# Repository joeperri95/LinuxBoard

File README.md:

# LinuxBoard

A basic stm32mp151 board to help me get more familiar with
- application processors 
- high speed digital design
- working with BGAs

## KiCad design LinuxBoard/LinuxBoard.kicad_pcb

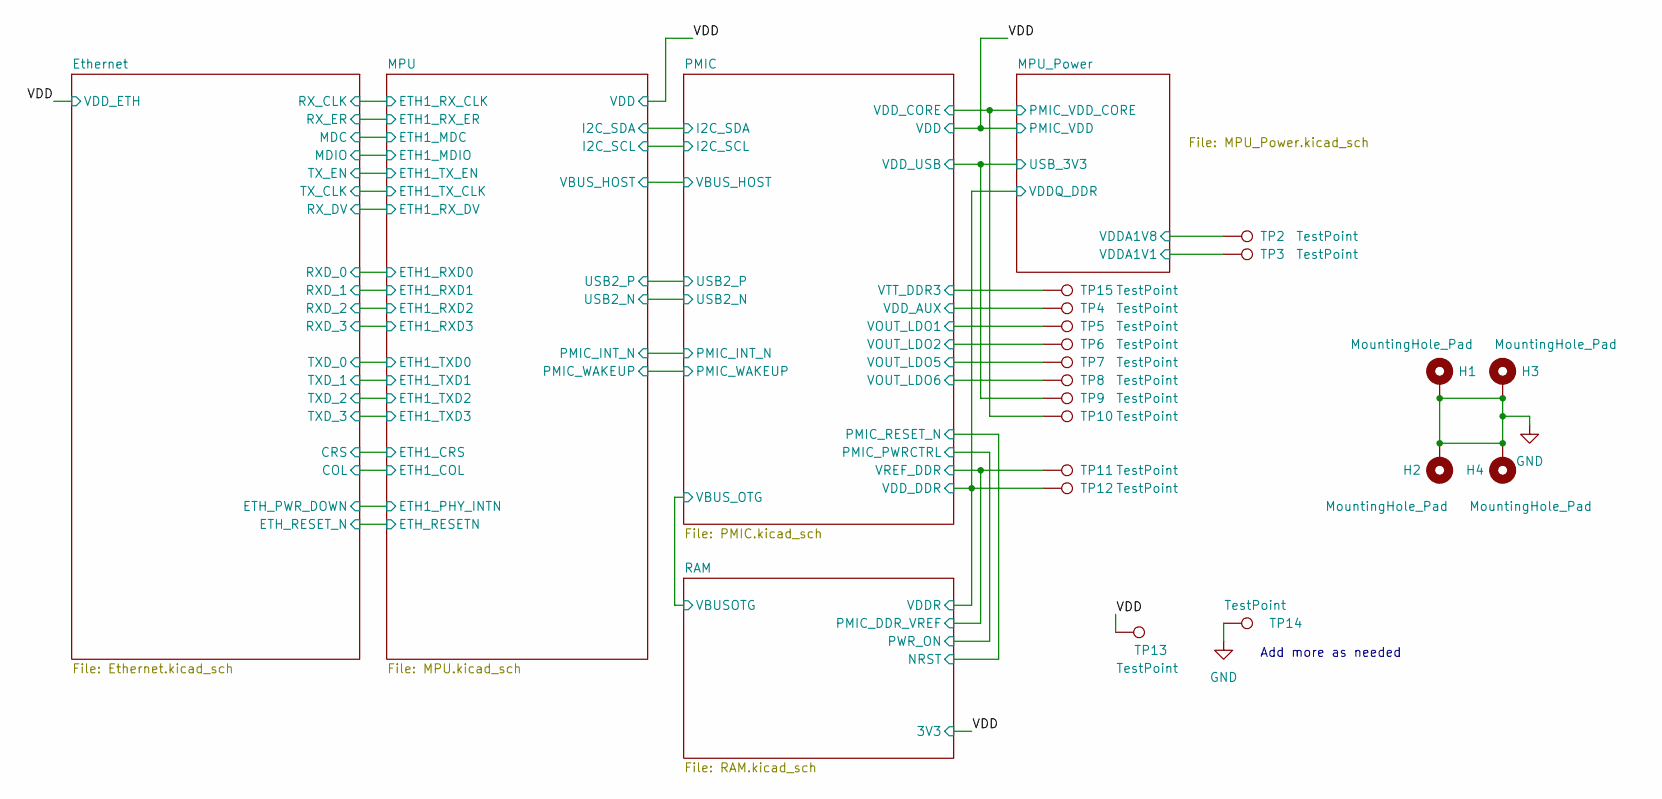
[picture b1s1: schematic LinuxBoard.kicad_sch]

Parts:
H1, H2, H3, H4: MountingHole_Pad; MountingHole_2.5mm_Pad
TP2, TP3, TP4, TP5, TP6, TP7, TP8, TP9, TP10, TP11, TP12, TP13, TP14, TP15: TestPoint; TestPoint_Pad_D2.0mm

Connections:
/MPU_Power/VDDA1V1: TP3.1; also elsewhere on the board
/MPU_Power/VDDA1V8: TP2.1; also elsewhere on the board
/MPU_Power/VDDQ_DDR: TP12.1; also elsewhere on the board
/MPU_Power/VDD_CORE: TP10.1; also elsewhere on the board
/PMIC/LDO1OUT: TP5.1; also elsewhere on the board
/PMIC/LDO2OUT: TP6.1; also elsewhere on the board
/PMIC/LDO3OUT: TP15.1; also elsewhere on the board
/PMIC/LDO4OUT: TP9.1; also elsewhere on the board
/PMIC/LDO5OUT: TP7.1; also elsewhere on the board
/PMIC/LDO6OUT: TP8.1; also elsewhere on the board
/PMIC/VDD_AUX: TP4.1; also elsewhere on the board
/PMIC/VREFDDR: TP11.1; also elsewhere on the board
/VDD: TP13.1; also elsewhere on the board
GND: H1.1, H2.1, H3.1, H4.1, TP14.1; also elsewhere on the board

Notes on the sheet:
Add more as needed

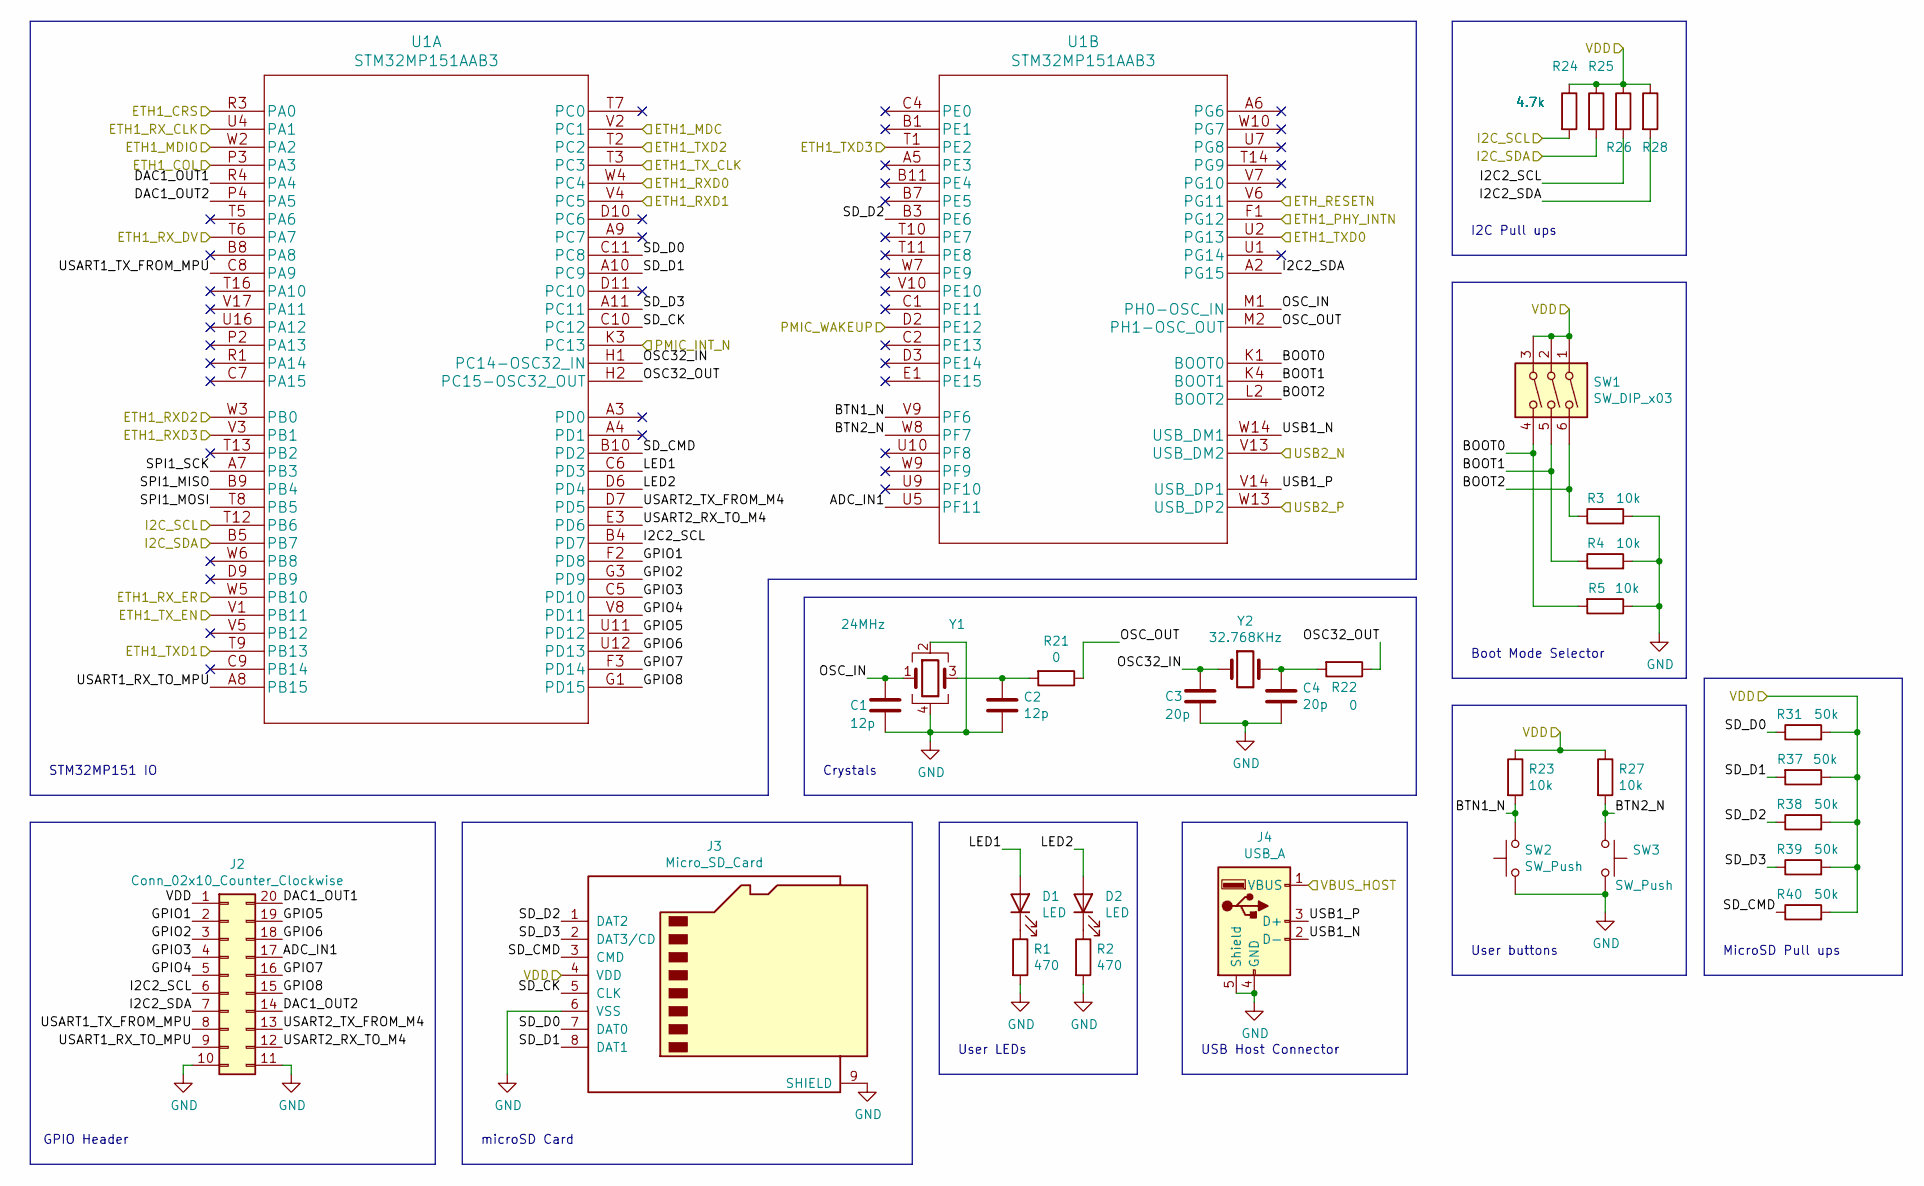
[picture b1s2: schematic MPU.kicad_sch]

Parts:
C1, C2: 12p; C_0603_1608Metric
C3, C4: 20p; C_0603_1608Metric
D1, D2: LED; LED_0603_1608Metric
J2: Conn_02x10_Counter_Clockwise; IDC-Header_2x10_P2.54mm_Vertical
J3: Micro_SD_Card; microSD_HC_Wuerth_693072010801
J4: USB_A; USB_A_Stewart_SS-52100-001_Horizontal
R1, R2: 470; R_0603_1608Metric_Pad0.98x0.95mm_HandSolder
R3, R4, R5, R23, R27: 10k; R_0603_1608Metric_Pad0.98x0.95mm_HandSolder
R21, R22: 0; R_0603_1608Metric_Pad0.98x0.95mm_HandSolder
R24, R25, R26, R28: 4.7k; R_0603_1608Metric_Pad0.98x0.95mm_HandSolder
R31, R37, R38, R39, R40: 50k; R_0603_1608Metric_Pad0.98x0.95mm_HandSolder
SW1: SW_DIP_x03; SW_DIP_SPSTx03_Slide_Omron_A6S-310x_W8.9mm_P2.54mm
SW2, SW3: SW_Push; SW_Push_1P1T_NO_6x6mm_H9.5mm
U1: STM32MP151AAB3
Y1: 24MHz; Crystal_SMD_2016-4Pin_2.0x1.6mm
Y2: 32.768KHz; Crystal_SMD_TXC_9HT11-2Pin_2.0x1.2mm

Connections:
/Ethernet/COL: U1.P3 (PA3); also elsewhere on the board
/Ethernet/CRS: U1.R3 (PA0); also elsewhere on the board
/Ethernet/ETH_PWR_DOWN: U1.F1 (PG12); also elsewhere on the board
/Ethernet/ETH_RESET_N: U1.V6 (PG11); also elsewhere on the board
/Ethernet/MDC: U1.V2 (PC1); also elsewhere on the board
/Ethernet/MDIO: U1.W2 (PA2); also elsewhere on the board
/Ethernet/RXD_0: U1.W4 (PC4); also elsewhere on the board
/Ethernet/RXD_1: U1.V4 (PC5); also elsewhere on the board
/Ethernet/RXD_2: U1.W3 (PB0); also elsewhere on the board
/Ethernet/RXD_3: U1.V3 (PB1); also elsewhere on the board
/Ethernet/RX_CLK: U1.U4 (PA1); also elsewhere on the board
/Ethernet/RX_DV: U1.T6 (PA7); also elsewhere on the board
/Ethernet/RX_ER: U1.W5 (PB10); also elsewhere on the board
/Ethernet/TXD_0: U1.U2 (PG13); also elsewhere on the board
/Ethernet/TXD_1: U1.T9 (PB13); also elsewhere on the board
/Ethernet/TXD_2: U1.T2 (PC2); also elsewhere on the board
/Ethernet/TXD_3: U1.T1 (PE2); also elsewhere on the board
/Ethernet/TX_CLK: U1.T3 (PC3); also elsewhere on the board
/Ethernet/TX_EN: U1.V1 (PB11); also elsewhere on the board
/MPU/ADC_IN1: J2.17, U1.U5 (PF11)
/MPU/BOOT0: R5.2, SW1.4, U1.K1 (BOOT0)
/MPU/BOOT1: R4.1, SW1.5, U1.K4 (BOOT1)
/MPU/BOOT2: R3.1, SW1.6, U1.L2 (BOOT2)
/MPU/BTN1_N: R23.2, SW2.2, U1.V9 (PF6)
/MPU/BTN2_N: R27.2, SW3.1, U1.W8 (PF7)
/MPU/DAC1_OUT1: J2.20, U1.R4 (PA4)
/MPU/DAC1_OUT2: J2.14, U1.P4 (PA5)
/MPU/GPIO1: J2.2, U1.F2 (PD8)
/MPU/GPIO2: J2.3, U1.G3 (PD9)
/MPU/GPIO3: J2.4, U1.C5 (PD10)
/MPU/GPIO4: J2.5, U1.V8 (PD11)
/MPU/GPIO5: J2.19, U1.U11 (PD12)
/MPU/GPIO6: J2.18, U1.U12 (PD13)
/MPU/GPIO7: J2.16, U1.F3 (PD14)
/MPU/GPIO8: J2.15, U1.G1 (PD15)
/MPU/I2C2_SCL: J2.6, R26.2, U1.B4 (PD7)
/MPU/I2C2_SDA: J2.7, R28.2, U1.A2 (PG15)
/MPU/I2C_SCL: R24.2, U1.T12 (PB6); also elsewhere on the board
/MPU/I2C_SDA: R25.2, U1.B5 (PB7); also elsewhere on the board
/MPU/LED1: D1.2 (A), U1.C6 (PD3)
/MPU/LED2: D2.2 (A), U1.D6 (PD4)
/MPU/OSC32_IN: C3.1, U1.H1 (PC14-OSC32_IN), Y2.1
/MPU/OSC32_OUT: R22.1, U1.H2 (PC15-OSC32_OUT)
/MPU/OSC_IN: C1.1, U1.M1 (PH0-OSC_IN), Y1.1
/MPU/OSC_OUT: R21.1, U1.M2 (PH1-OSC_OUT)
/MPU/PMIC_INT_N: U1.K3 (PC13); also elsewhere on the board
/MPU/PMIC_WAKEUP: U1.D2 (PE12); also elsewhere on the board
/MPU/SD_CK: J3.5 (CLK), U1.C10 (PC12)
/MPU/SD_CMD: J3.3 (CMD), R40.1, U1.B10 (PD2)
/MPU/SD_D0: J3.7 (DAT0), R31.1, U1.C11 (PC8)
/MPU/SD_D1: J3.8 (DAT1), R37.2, U1.A10 (PC9)
/MPU/SD_D2: J3.1 (DAT2), R38.1, U1.B3 (PE6)
/MPU/SD_D3: J3.2 (DAT3/CD), R39.1, U1.A11 (PC11)
/MPU/SPI1_MISO: U1.B9 (PB4)
/MPU/SPI1_MOSI: U1.T8 (PB5)
/MPU/SPI1_SCK: U1.A7 (PB3)
/MPU/USART1_RX_TO_MPU: J2.9, U1.A8 (PB15)
/MPU/USART1_TX_FROM_MPU: J2.8, U1.C8 (PA9)
/MPU/USART2_RX_TO_M4: J2.12, U1.E3 (PD6)
/MPU/USART2_TX_FROM_M4: J2.13, U1.D7 (PD5)
/MPU/USB1_N: J4.2 (D-), U1.W14 (USB_DM1)
/MPU/USB1_P: J4.3 (D+), U1.V14 (USB_DP1)
/MPU/USB2_N: U1.V13 (USB_DM2); also elsewhere on the board
/MPU/USB2_P: U1.W13 (USB_DP2); also elsewhere on the board
/MPU/VBUS_HOST: J4.1 (VBUS); also elsewhere on the board
/VDD: J2.1, J3.4 (VDD), R23.1, R24.1, R25.1, R26.1, R27.1, R28.1, R31.2, R37.1, R38.2, R39.2, R40.2, SW1.1, SW1.2, SW1.3; also elsewhere on the board
GND: C1.2, C2.2, C3.2, C4.2, J2.10, J2.11, J3.6 (VSS), J3.9 (SHIELD), J4.4 (GND), J4.5 (Shield), R1.2, R2.2, R3.2, R4.2, R5.1, SW2.1, SW3.2, Y1.2, Y1.4; also elsewhere on the board
unnamed: C2.1, R21.2, Y1.3
unnamed: C4.1, R22.2, Y2.2
unnamed: D1.1 (K), R1.1
unnamed: D2.1 (K), R2.1

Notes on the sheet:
Crystals
MicroSD Pull ups
GPIO Header
User LEDs
STM32MP151 IO
I2C Pull ups
USB Host Connector
Boot Mode Selector
microSD Card
User buttons

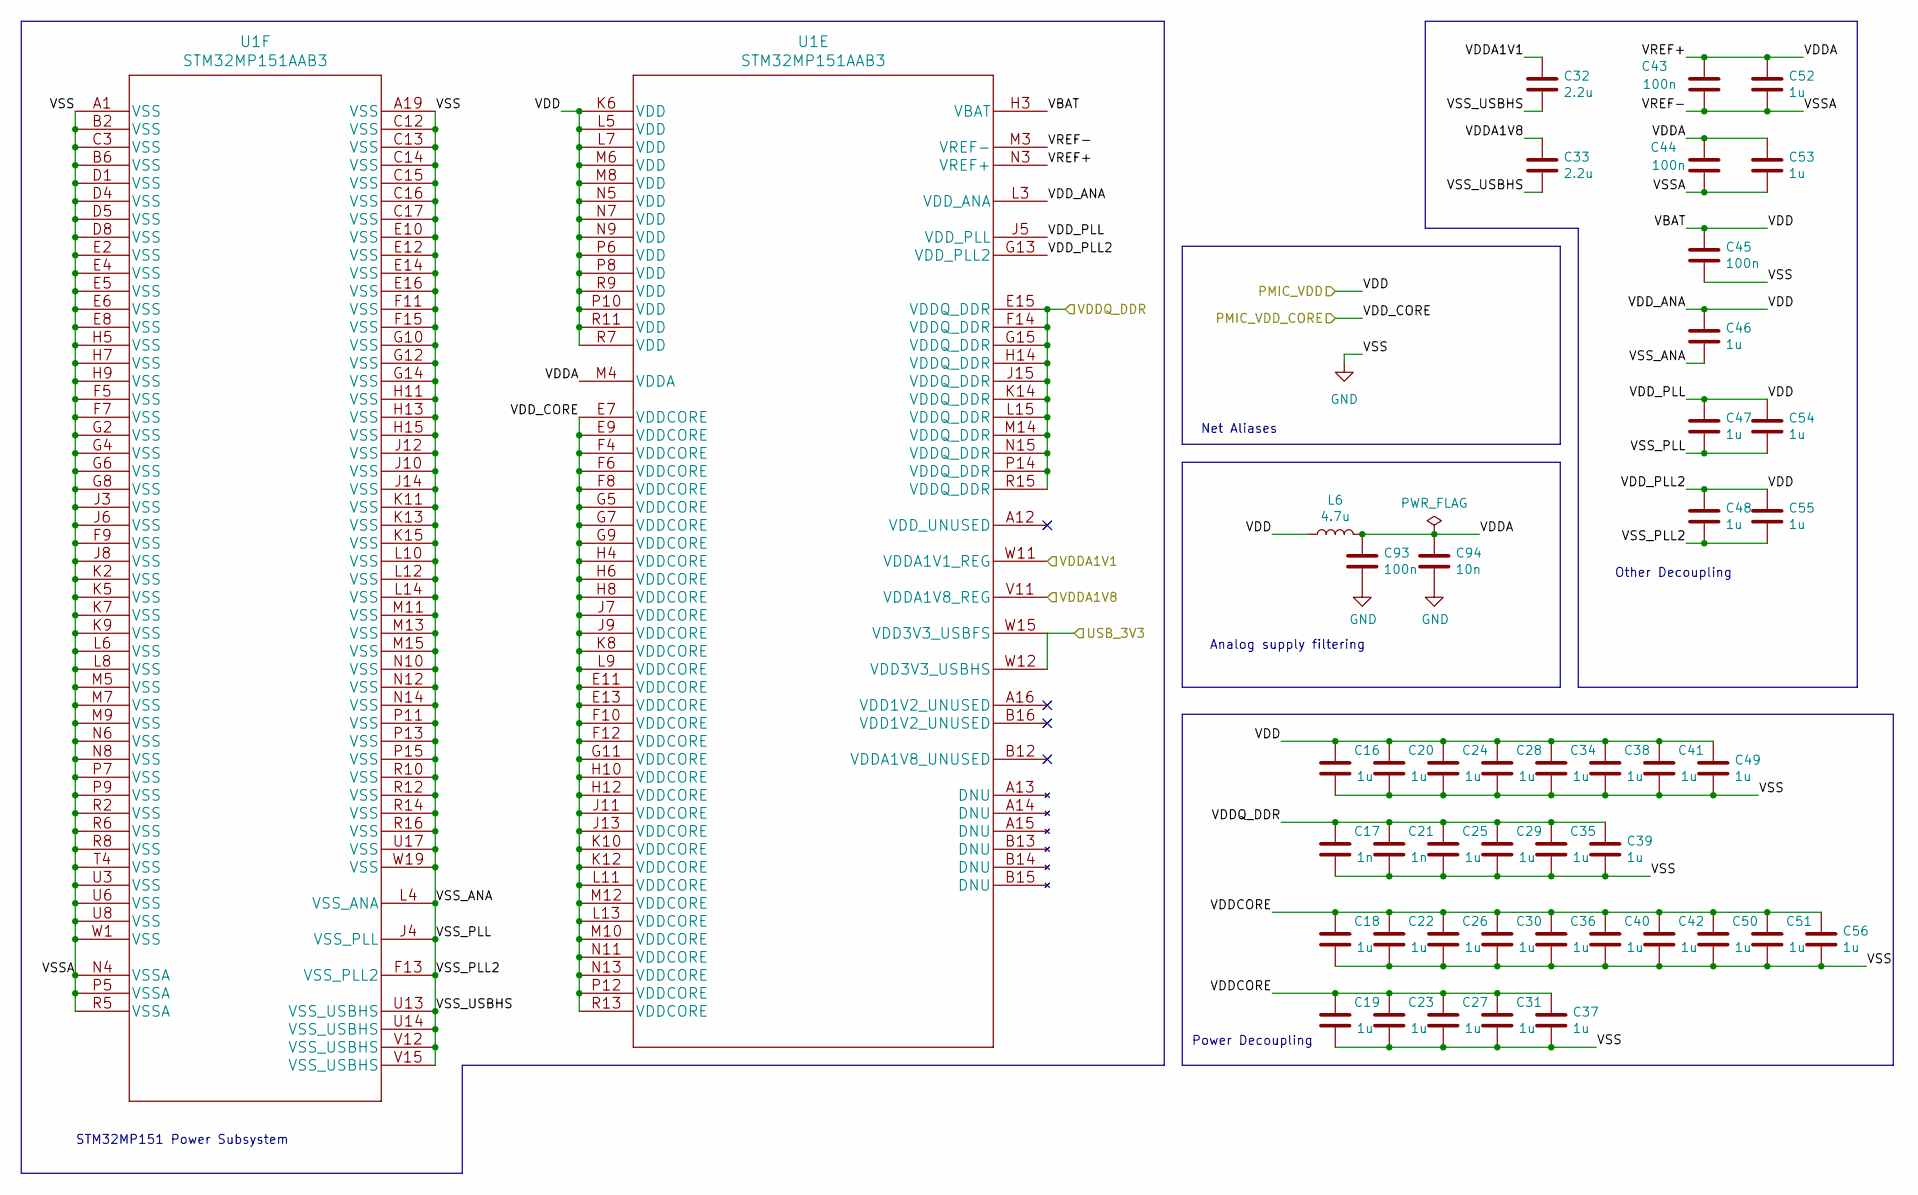
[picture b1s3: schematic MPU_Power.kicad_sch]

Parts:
C16, C18, C19, C20, C22, C23, C24, C25, C26, C27, C28, C29, C30, C31, C34, C35, C36, C37, C38, C39, C40, C41, C42, C46, C47, C48, C49, C50, C51, C52, C53, C54, C55, C56: 1u; C_0603_1608Metric
C17, C21: 1n; C_0603_1608Metric
C32, C33: 2.2u; C_0603_1608Metric
C43, C44, C45, C93: 100n; C_0603_1608Metric
C94: 10n; C_0603_1608Metric
L6: 4.7u; L_0603_1608Metric
U1: STM32MP151AAB3

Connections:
/MPU_Power/VDDA: C43.2, C44.2, C52.1, C53.1, C93.1, C94.1, L6.2, U1.M4 (VDDA), U1.N3 (VREF+)
/MPU_Power/VDDA1V1: C32.1, U1.W11 (VDDA1V1_REG); also elsewhere on the board
/MPU_Power/VDDA1V8: C33.1, U1.V11 (VDDA1V8_REG); also elsewhere on the board
/MPU_Power/VDDCORE: C18.1, C19.1, C22.1, C23.1, C26.1, C27.1, C30.1, C31.1, C36.1, C37.1, C40.1, C42.1, C50.1, C51.1, C56.1
/MPU_Power/VDDQ_DDR: C17.1, C21.1, C25.1, C29.1, C35.1, C39.1, U1.E15 (VDDQ_DDR), U1.F14 (VDDQ_DDR), U1.G15 (VDDQ_DDR), U1.H14 (VDDQ_DDR), U1.J15 (VDDQ_DDR), U1.K14 (VDDQ_DDR), U1.L15 (VDDQ_DDR), U1.M14 (VDDQ_DDR), U1.N15 (VDDQ_DDR), U1.P14 (VDDQ_DDR), U1.R15 (VDDQ_DDR); also elsewhere on the board
/MPU_Power/VDD_CORE: U1.E7 (VDDCORE), U1.E9 (VDDCORE), U1.E11 (VDDCORE), U1.E13 (VDDCORE), U1.F4 (VDDCORE), U1.F6 (VDDCORE), U1.F8 (VDDCORE), U1.F10 (VDDCORE), U1.F12 (VDDCORE), U1.G5 (VDDCORE), U1.G7 (VDDCORE), U1.G9 (VDDCORE), U1.G11 (VDDCORE), U1.H4 (VDDCORE), U1.H6 (VDDCORE), U1.H8 (VDDCORE), U1.H10 (VDDCORE), U1.H12 (VDDCORE), U1.J7 (VDDCORE), U1.J9 (VDDCORE), U1.J11 (VDDCORE), U1.J13 (VDDCORE), U1.K8 (VDDCORE), U1.K10 (VDDCORE), U1.K12 (VDDCORE), U1.L9 (VDDCORE), U1.L11 (VDDCORE), U1.L13 (VDDCORE), U1.M10 (VDDCORE), U1.M12 (VDDCORE), U1.N11 (VDDCORE), U1.N13 (VDDCORE), U1.P12 (VDDCORE), U1.R13 (VDDCORE); also elsewhere on the board
/PMIC/LDO4OUT: U1.W12 (VDD3V3_USBHS), U1.W15 (VDD3V3_USBFS); also elsewhere on the board
/VDD: C16.1, C20.1, C24.1, C28.1, C34.1, C38.1, C41.1, C45.1, C46.1, C47.1, C48.1, C49.1, C54.1, C55.1, L6.1, U1.G13 (VDD_PLL2), U1.H3 (VBAT), U1.J5 (VDD_PLL), U1.K6 (VDD), U1.L3 (VDD_ANA), U1.L5 (VDD), U1.L7 (VDD), U1.M6 (VDD), U1.M8 (VDD), U1.N5 (VDD), U1.N7 (VDD), U1.N9 (VDD), U1.P6 (VDD), U1.P8 (VDD), U1.P10 (VDD), U1.R7 (VDD), U1.R9 (VDD), U1.R11 (VDD); also elsewhere on the board
GND: C16.2, C17.2, C18.2, C19.2, C20.2, C21.2, C22.2, C23.2, C24.2, C25.2, C26.2, C27.2, C28.2, C29.2, C30.2, C31.2, C32.2, C33.2, C34.2, C35.2, C36.2, C37.2, C38.2, C39.2, C40.2, C41.2, C42.2, C43.1, C44.1, C45.2, C46.2, C47.2, C48.2, C49.2, C50.2, C51.2, C52.2, C53.2, C54.2, C55.2, C56.2, C93.2, C94.2, U1.A1 (VSS), U1.A19 (VSS), U1.B2 (VSS), U1.B6 (VSS), U1.C3 (VSS), U1.C12 (VSS), U1.C13 (VSS), U1.C14 (VSS), U1.C15 (VSS), U1.C16 (VSS), U1.C17 (VSS), U1.D1 (VSS), U1.D4 (VSS), U1.D5 (VSS), U1.D8 (VSS), U1.E2 (VSS), U1.E4 (VSS), U1.E5 (VSS), U1.E6 (VSS), U1.E8 (VSS), U1.E10 (VSS), U1.E12 (VSS), U1.E14 (VSS), U1.E16 (VSS), U1.F5 (VSS), U1.F7 (VSS), U1.F9 (VSS), U1.F11 (VSS), U1.F13 (VSS_PLL2), U1.F15 (VSS), U1.G2 (VSS), U1.G4 (VSS), U1.G6 (VSS), U1.G8 (VSS), U1.G10 (VSS), U1.G12 (VSS), U1.G14 (VSS), U1.H5 (VSS), U1.H7 (VSS), U1.H9 (VSS), U1.H11 (VSS), U1.H13 (VSS), U1.H15 (VSS), U1.J3 (VSS), U1.J4 (VSS_PLL), U1.J6 (VSS), U1.J8 (VSS), U1.J10 (VSS), U1.J12 (VSS), U1.J14 (VSS), U1.K2 (VSS), U1.K5 (VSS), U1.K7 (VSS), U1.K9 (VSS), U1.K11 (VSS), U1.K13 (VSS), U1.K15 (VSS), U1.L4 (VSS_ANA), U1.L6 (VSS), U1.L8 (VSS), U1.L10 (VSS), U1.L12 (VSS), U1.L14 (VSS), U1.M3 (VREF-), U1.M5 (VSS), U1.M7 (VSS), U1.M9 (VSS), U1.M11 (VSS), U1.M13 (VSS), U1.M15 (VSS), U1.N4 (VSSA), U1.N6 (VSS), U1.N8 (VSS), U1.N10 (VSS), U1.N12 (VSS), U1.N14 (VSS), U1.P5 (VSSA), U1.P7 (VSS), U1.P9 (VSS), U1.P11 (VSS), U1.P13 (VSS), U1.P15 (VSS), U1.R2 (VSS), U1.R5 (VSSA), U1.R6 (VSS), U1.R8 (VSS), U1.R10 (VSS), U1.R12 (VSS), U1.R14 (VSS), U1.R16 (VSS), U1.T4 (VSS), U1.U3 (VSS), U1.U6 (VSS), U1.U8 (VSS), U1.U13 (VSS_USBHS), U1.U14 (VSS_USBHS), U1.U17 (VSS), U1.V12 (VSS_USBHS), U1.V15 (VSS_USBHS), U1.W1 (VSS), U1.W19 (VSS); also elsewhere on the board

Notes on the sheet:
STM32MP151 Power Subsystem
Net Aliases
Analog supply filtering
Other Decoupling
Power Decoupling

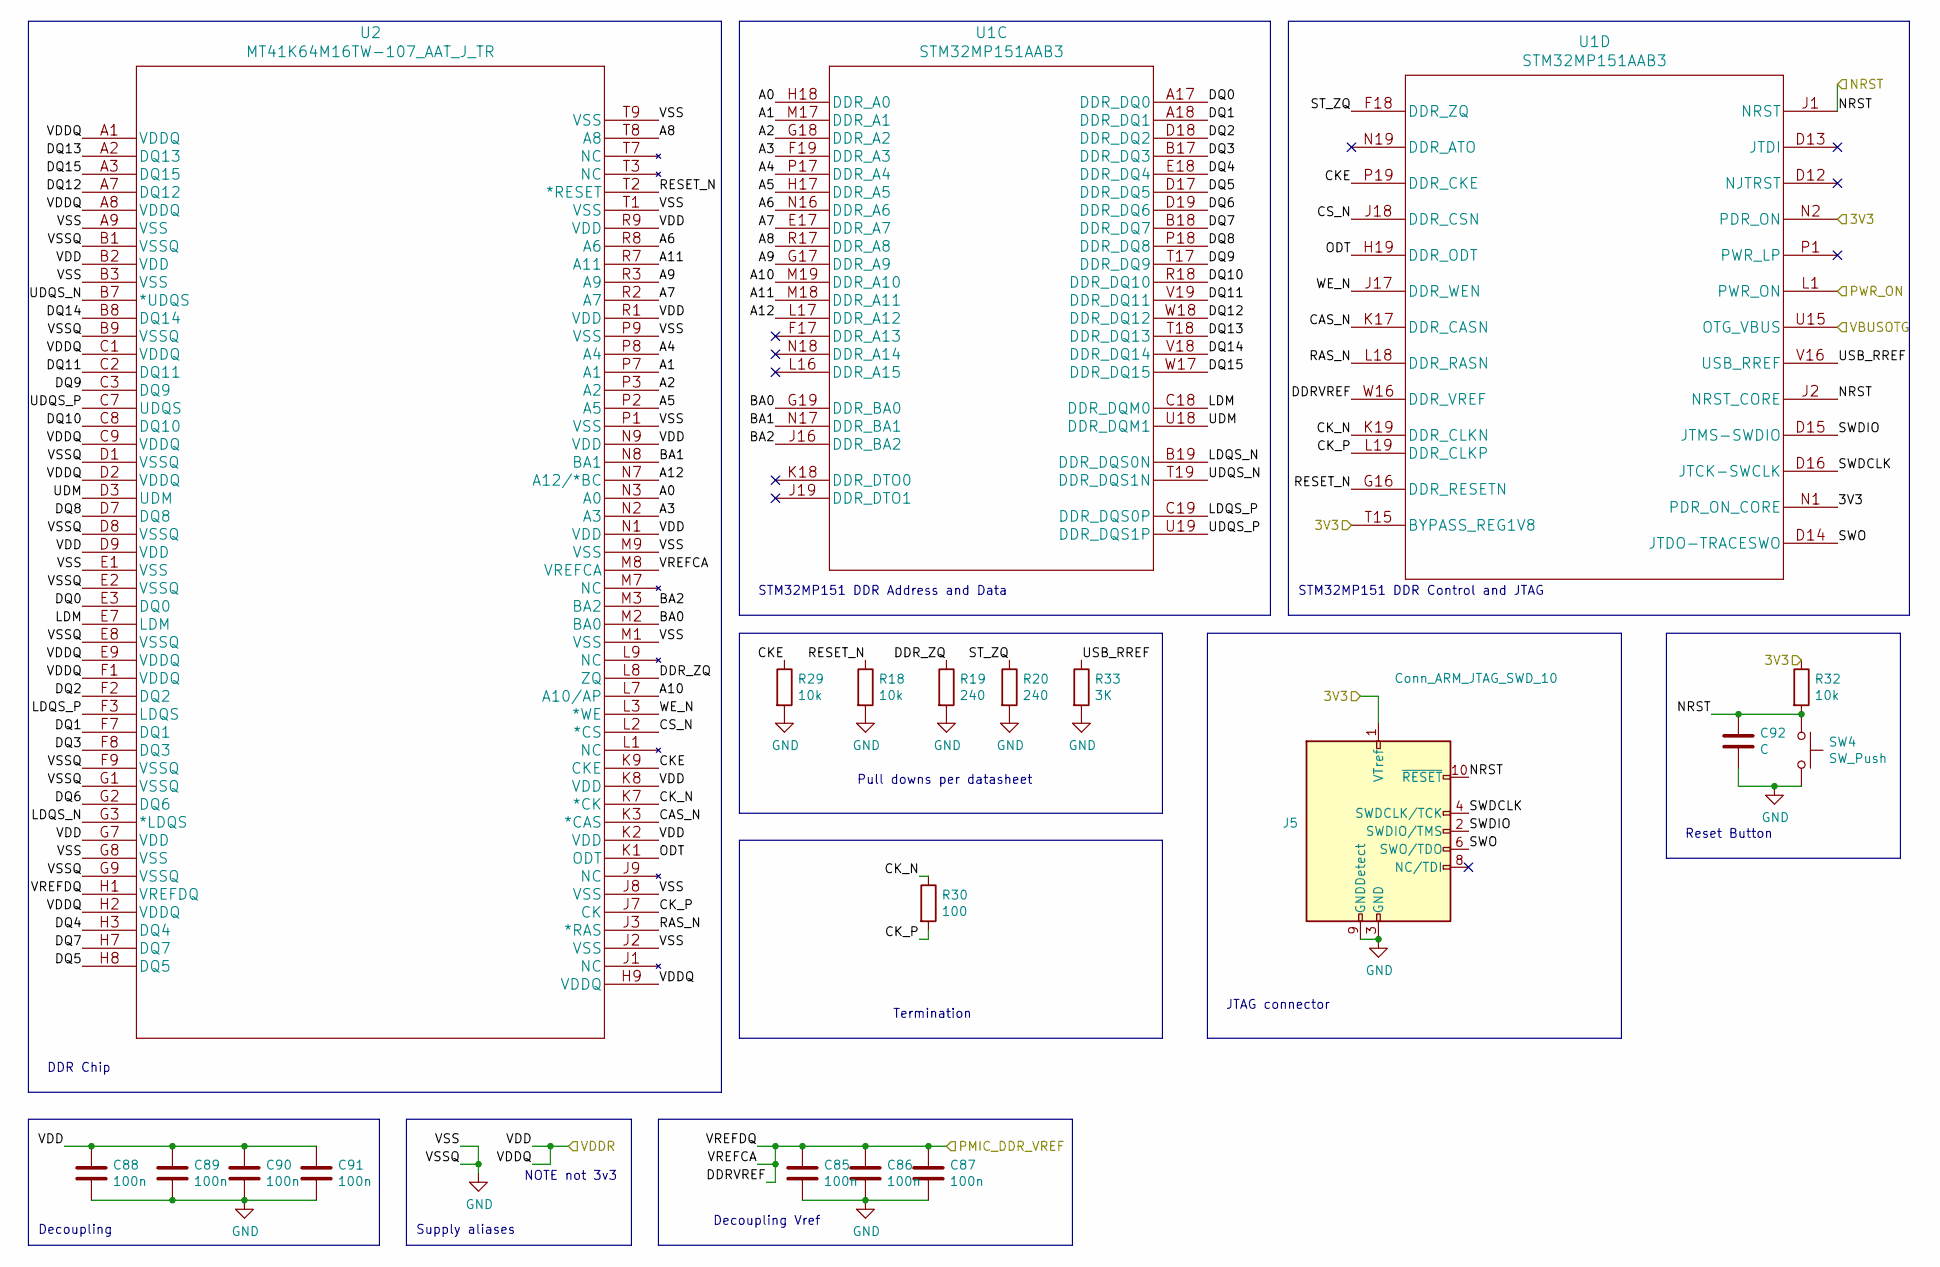
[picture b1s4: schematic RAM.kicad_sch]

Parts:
C85, C86, C87, C88, C89, C90, C91: 100n; C_0603_1608Metric
C92: C; C_0603_1608Metric
J5: Conn_ARM_JTAG_SWD_10; PinHeader_2x05_P1.27mm_Vertical_SMD
R18, R29, R32: 10k; R_0603_1608Metric_Pad0.98x0.95mm_HandSolder
R19, R20: 240; R_0603_1608Metric_Pad0.98x0.95mm_HandSolder
R30: 100; R_0603_1608Metric_Pad0.98x0.95mm_HandSolder
R33: 3K; R_0603_1608Metric_Pad0.98x0.95mm_HandSolder
SW4: SW_Push; SW_Push_1P1T_NO_6x6mm_H9.5mm
U1: STM32MP151AAB3
U2: MT41K64M16TW-107_AAT_J_TR

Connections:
/MPU_Power/VDDQ_DDR: C88.1, C89.1, C90.1, C91.1, U2.A1 (VDDQ), U2.A8 (VDDQ), U2.B2 (VDD), U2.C1 (VDDQ), U2.C9 (VDDQ), U2.D2 (VDDQ), U2.D9 (VDD), U2.E9 (VDDQ), U2.F1 (VDDQ), U2.G7 (VDD), U2.H2 (VDDQ), U2.H9 (VDDQ), U2.K2 (VDD), U2.K8 (VDD), U2.N1 (VDD), U2.N9 (VDD), U2.R1 (VDD), U2.R9 (VDD); also elsewhere on the board
/PMIC/PMIC_PWRCTRL: U1.L1 (PWR_ON); also elsewhere on the board
/PMIC/VBUSOTG: U1.U15 (OTG_VBUS); also elsewhere on the board
/PMIC/VREFDDR: C85.1, C86.1, C87.1, U1.W16 (DDR_VREF), U2.H1 (VREFDQ), U2.M8 (VREFCA); also elsewhere on the board
/RAM/A0: U1.H18 (DDR_A0), U2.N3 (A0)
/RAM/A1: U1.M17 (DDR_A1), U2.P7 (A1)
/RAM/A2: U1.G18 (DDR_A2), U2.P3 (A2)
/RAM/A3: U1.F19 (DDR_A3), U2.N2 (A3)
/RAM/A4: U1.P17 (DDR_A4), U2.P8 (A4)
/RAM/A5: U1.H17 (DDR_A5), U2.P2 (A5)
/RAM/A6: U1.N16 (DDR_A6), U2.R8 (A6)
/RAM/A7: U1.E17 (DDR_A7), U2.R2 (A7)
/RAM/A8: U1.R17 (DDR_A8), U2.T8 (A8)
/RAM/A9: U1.G17 (DDR_A9), U2.R3 (A9)
/RAM/A10: U1.M19 (DDR_A10), U2.L7 (A10/AP)
/RAM/A11: U1.M18 (DDR_A11), U2.R7 (A11)
/RAM/A12: U1.L17 (DDR_A12), U2.N7 (A12/*BC)
/RAM/BA0: U1.G19 (DDR_BA0), U2.M2 (BA0)
/RAM/BA1: U1.N17 (DDR_BA1), U2.N8 (BA1)
/RAM/BA2: U1.J16 (DDR_BA2), U2.M3 (BA2)
/RAM/CAS_N: U1.K17 (DDR_CASN), U2.K3 (*CAS)
/RAM/CKE: R29.1, U1.P19 (DDR_CKE), U2.K9 (CKE)
/RAM/CK_N: R30.1, U1.K19 (DDR_CLKN), U2.K7 (*CK)
/RAM/CK_P: R30.2, U1.L19 (DDR_CLKP), U2.J7 (CK)
/RAM/CS_N: U1.J18 (DDR_CSN), U2.L2 (*CS)
/RAM/DDR_ZQ: R19.1, U2.L8 (ZQ)
/RAM/DQ0: U1.A17 (DDR_DQ0), U2.E3 (DQ0)
/RAM/DQ1: U1.A18 (DDR_DQ1), U2.F7 (DQ1)
/RAM/DQ2: U1.D18 (DDR_DQ2), U2.F2 (DQ2)
/RAM/DQ3: U1.B17 (DDR_DQ3), U2.F8 (DQ3)
/RAM/DQ4: U1.E18 (DDR_DQ4), U2.H3 (DQ4)
/RAM/DQ5: U1.D17 (DDR_DQ5), U2.H8 (DQ5)
/RAM/DQ6: U1.D19 (DDR_DQ6), U2.G2 (DQ6)
/RAM/DQ7: U1.B18 (DDR_DQ7), U2.H7 (DQ7)
/RAM/DQ8: U1.P18 (DDR_DQ8), U2.D7 (DQ8)
/RAM/DQ9: U1.T17 (DDR_DQ9), U2.C3 (DQ9)
/RAM/DQ10: U1.R18 (DDR_DQ10), U2.C8 (DQ10)
/RAM/DQ11: U1.V19 (DDR_DQ11), U2.C2 (DQ11)
/RAM/DQ12: U1.W18 (DDR_DQ12), U2.A7 (DQ12)
/RAM/DQ13: U1.T18 (DDR_DQ13), U2.A2 (DQ13)
/RAM/DQ14: U1.V18 (DDR_DQ14), U2.B8 (DQ14)
/RAM/DQ15: U1.W17 (DDR_DQ15), U2.A3 (DQ15)
/RAM/LDM: U1.C18 (DDR_DQM0), U2.E7 (LDM)
/RAM/LDQS_N: U1.B19 (DDR_DQS0N), U2.G3 (*LDQS)
/RAM/LDQS_P: U1.C19 (DDR_DQS0P), U2.F3 (LDQS)
/RAM/NRST: C92.1, J5.10 (~RESET), R32.2, SW4.1, U1.J1 (NRST), U1.J2 (NRST_CORE); also elsewhere on the board
/RAM/ODT: U1.H19 (DDR_ODT), U2.K1 (ODT)
/RAM/RAS_N: U1.L18 (DDR_RASN), U2.J3 (*RAS)
/RAM/RESET_N: R18.1, U1.G16 (DDR_RESETN), U2.T2 (*RESET)
/RAM/ST_ZQ: R20.1, U1.F18 (DDR_ZQ)
/RAM/SWDCLK: J5.4 (SWDCLK/TCK), U1.D16 (JTCK-SWCLK)
/RAM/SWDIO: J5.2 (SWDIO/TMS), U1.D15 (JTMS-SWDIO)
/RAM/SWO: J5.6 (SWO/TDO), U1.D14 (JTDO-TRACESWO)
/RAM/UDM: U1.U18 (DDR_DQM1), U2.D3 (UDM)
/RAM/UDQS_N: U1.T19 (DDR_DQS1N), U2.B7 (*UDQS)
/RAM/UDQS_P: U1.U19 (DDR_DQS1P), U2.C7 (UDQS)
/RAM/USB_RREF: R33.1, U1.V16 (USB_RREF)
/RAM/WE_N: U1.J17 (DDR_WEN), U2.L3 (*WE)
/VDD: J5.1 (VTref), R32.1, U1.N1 (PDR_ON_CORE), U1.N2 (PDR_ON), U1.T15 (BYPASS_REG1V8); also elsewhere on the board
GND: C85.2, C86.2, C87.2, C88.2, C89.2, C90.2, C91.2, C92.2, J5.3 (GND), J5.5 (GND), J5.9 (GNDDetect), R18.2, R19.2, R20.2, R29.2, R33.2, SW4.2, U2.A9 (VSS), U2.B1 (VSSQ), U2.B3 (VSS), U2.B9 (VSSQ), U2.D1 (VSSQ), U2.D8 (VSSQ), U2.E1 (VSS), U2.E2 (VSSQ), U2.E8 (VSSQ), U2.F9 (VSSQ), U2.G1 (VSSQ), U2.G8 (VSS), U2.G9 (VSSQ), U2.J2 (VSS), U2.J8 (VSS), U2.M1 (VSS), U2.M9 (VSS), U2.P1 (VSS), U2.P9 (VSS), U2.T1 (VSS), U2.T9 (VSS); also elsewhere on the board

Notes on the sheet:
JTAG connector
Reset Button
Decoupling Vref
Termination
STM32MP151 DDR Control and JTAG
STM32MP151 DDR Address and Data
Supply aliases
NOTE not 3v3
DDR Chip
Decoupling
Pull downs per datasheet

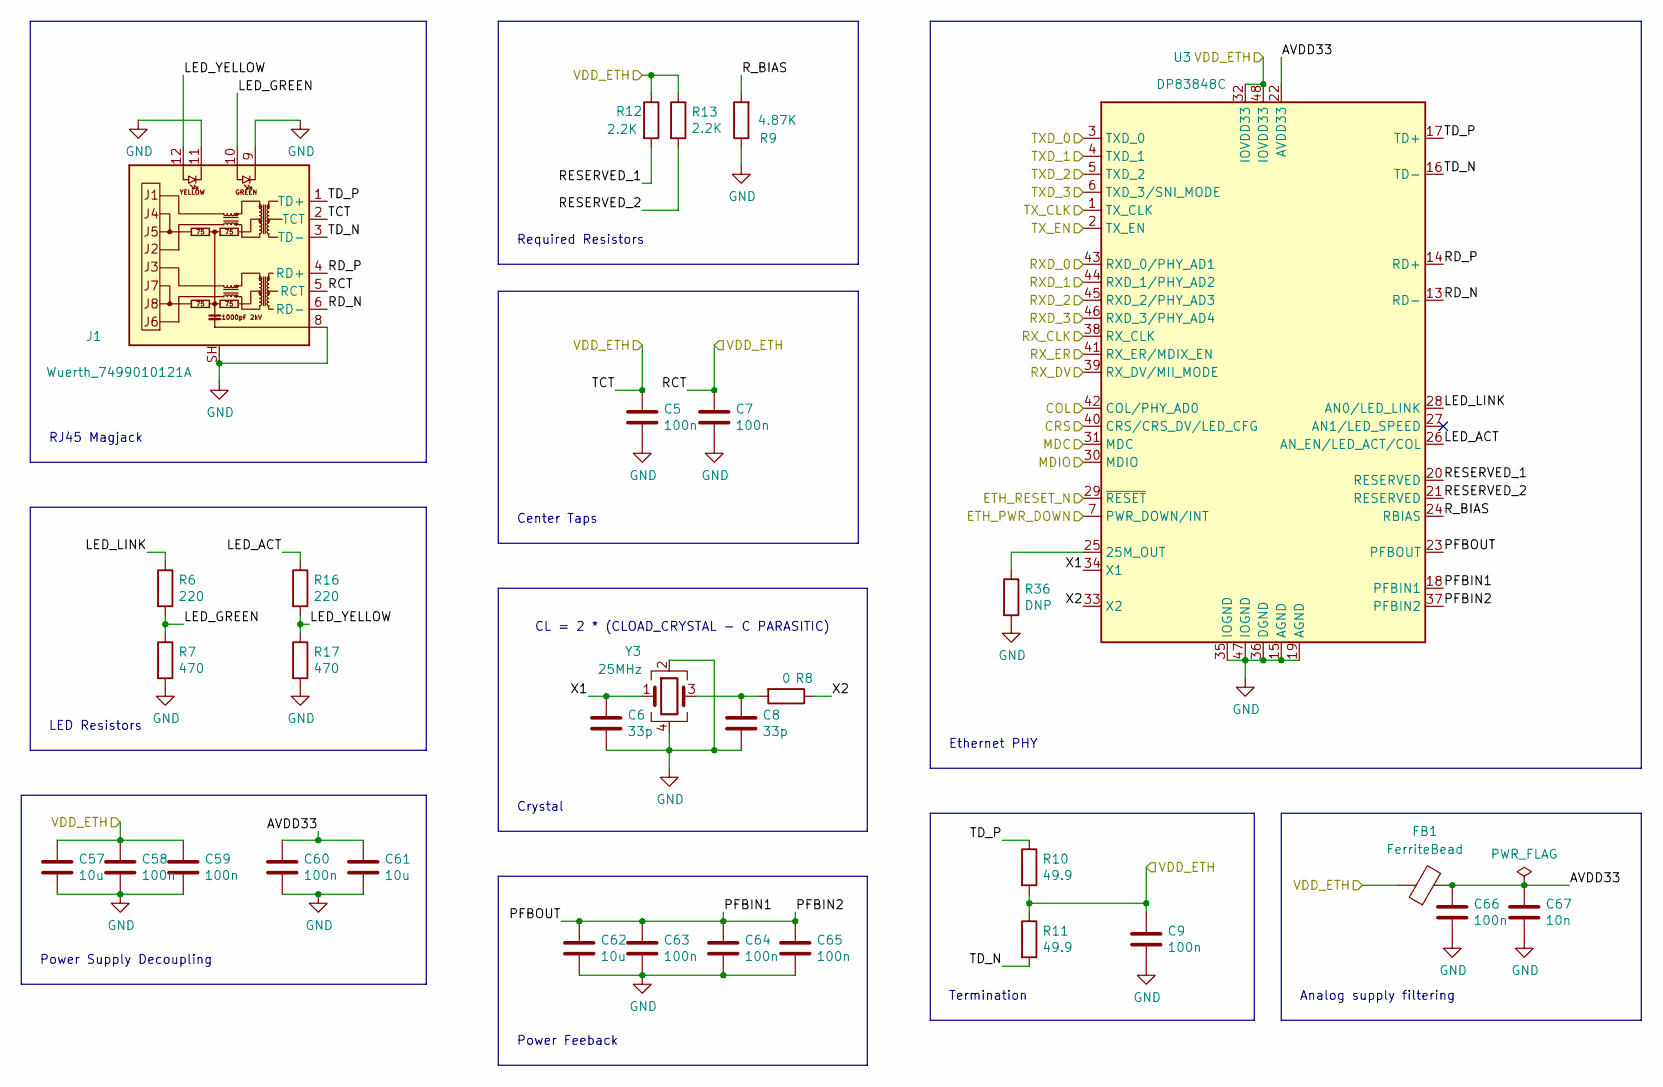
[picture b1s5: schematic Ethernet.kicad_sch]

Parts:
C5, C7, C9, C58, C59, C60, C63, C64, C65, C66: 100n; C_0603_1608Metric
C6, C8: 33p; C_0603_1608Metric
C57, C61, C62: 10u; C_0603_1608Metric
C67: 10n; C_0603_1608Metric
FB1: FerriteBead; L_0603_1608Metric_Pad1.05x0.95mm_HandSolder
J1: Wuerth_7499010121A; RJ45_Wuerth_7499010121A_Horizontal
R6, R16: 220; R_0603_1608Metric_Pad0.98x0.95mm_HandSolder
R7, R17: 470; R_0603_1608Metric_Pad0.98x0.95mm_HandSolder
R8: 0; R_0603_1608Metric_Pad0.98x0.95mm_HandSolder
R9: 4.87K; R_0603_1608Metric_Pad0.98x0.95mm_HandSolder
R10, R11: 49.9; R_0603_1608Metric_Pad0.98x0.95mm_HandSolder
R12, R13: 2.2K; R_0603_1608Metric_Pad0.98x0.95mm_HandSolder
R36: DNP; R_0603_1608Metric_Pad0.98x0.95mm_HandSolder
U3: DP83848C; LQFP-48_7x7mm_P0.5mm
Y3: 25MHz; Crystal_SMD_3225-4Pin_3.2x2.5mm

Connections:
/Ethernet/AVDD33: C60.1, C61.1, C66.1, C67.1, FB1.2, U3.22 (AVDD33)
/Ethernet/COL: U3.42 (COL/PHY_AD0); also elsewhere on the board
/Ethernet/CRS: U3.40 (CRS/CRS_DV/LED_CFG); also elsewhere on the board
/Ethernet/ETH_PWR_DOWN: U3.7 (PWR_DOWN/INT); also elsewhere on the board
/Ethernet/ETH_RESET_N: U3.29 (~RESET); also elsewhere on the board
/Ethernet/LED_ACT: R16.1, U3.26 (AN_EN/LED_ACT/COL)
/Ethernet/LED_GREEN: J1.10, R6.2, R7.1
/Ethernet/LED_LINK: R6.1, U3.28 (AN0/LED_LINK)
/Ethernet/LED_YELLOW: J1.12, R16.2, R17.1
/Ethernet/MDC: U3.31 (MDC); also elsewhere on the board
/Ethernet/MDIO: U3.30 (MDIO); also elsewhere on the board
/Ethernet/PFBIN1: C62.1, C63.1, C64.1, C65.1, U3.18 (PFBIN1), U3.23 (PFBOUT), U3.37 (PFBIN2)
/Ethernet/RD_N: J1.6 (RD-), U3.13 (RD-)
/Ethernet/RD_P: J1.4 (RD+), U3.14 (RD+)
/Ethernet/RESERVED_1: R12.2, U3.20 (RESERVED)
/Ethernet/RESERVED_2: R13.2, U3.21 (RESERVED)
/Ethernet/RXD_0: U3.43 (RXD_0/PHY_AD1); also elsewhere on the board
/Ethernet/RXD_1: U3.44 (RXD_1/PHY_AD2); also elsewhere on the board
/Ethernet/RXD_2: U3.45 (RXD_2/PHY_AD3); also elsewhere on the board
/Ethernet/RXD_3: U3.46 (RXD_3/PHY_AD4); also elsewhere on the board
/Ethernet/RX_CLK: U3.38 (RX_CLK); also elsewhere on the board
/Ethernet/RX_DV: U3.39 (RX_DV/MII_MODE); also elsewhere on the board
/Ethernet/RX_ER: U3.41 (RX_ER/MDIX_EN); also elsewhere on the board
/Ethernet/R_BIAS: R9.2, U3.24 (RBIAS)
/Ethernet/TD_N: J1.3 (TD-), R11.2, U3.16 (TD-)
/Ethernet/TD_P: J1.1 (TD+), R10.1, U3.17 (TD+)
/Ethernet/TXD_0: U3.3 (TXD_0); also elsewhere on the board
/Ethernet/TXD_1: U3.4 (TXD_1); also elsewhere on the board
/Ethernet/TXD_2: U3.5 (TXD_2); also elsewhere on the board
/Ethernet/TXD_3: U3.6 (TXD_3/SNI_MODE); also elsewhere on the board
/Ethernet/TX_CLK: U3.1 (TX_CLK); also elsewhere on the board
/Ethernet/TX_EN: U3.2 (TX_EN); also elsewhere on the board
/Ethernet/X1: C6.1, U3.34 (X1), Y3.1
/Ethernet/X2: R8.1, U3.33 (X2)
/VDD: C5.1, C7.1, C9.1, C57.1, C58.1, C59.1, FB1.1, J1.2 (TCT), J1.5 (RCT), R10.2, R11.1, R12.1, R13.1, U3.32 (IOVDD33), U3.48 (IOVDD33); also elsewhere on the board
GND: C5.2, C6.2, C7.2, C8.2, C9.2, C57.2, C58.2, C59.2, C60.2, C61.2, C62.2, C63.2, C64.2, C65.2, C66.2, C67.2, J1.8, J1.9, J1.11, J1.SH, R7.2, R9.1, R17.2, R36.2, U3.15 (AGND), U3.19 (AGND), U3.35 (IOGND), U3.36 (DGND), U3.47 (IOGND), Y3.2, Y3.4; also elsewhere on the board
unnamed: C8.1, R8.2, Y3.3
unnamed: R36.1, U3.25 (25M_OUT)

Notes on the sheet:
Center Taps
CL = 2 * (CLOAD_CRYSTAL - C PARASITIC)
Power Supply Decoupling
Crystal
Required Resistors
Termination
Ethernet PHY
RJ45 Magjack
Analog supply filtering
LED Resistors
Power Feeback

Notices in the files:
parts and their libraries:
Copyright 2016 Accelerated Designs. All rights reserved.
